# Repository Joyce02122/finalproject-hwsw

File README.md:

# DreamGuard: PTSD Lucid Dreaming Aid

The DreamGuard is a wearable device that helps people with PTSD manage nightmares using lucid dreaming techniques. It detects nightmares through heart rate or MPU6050 sensors and uses gentle light or sound stimuli to trigger awareness, allowing users to regain control. This device aims to reduce emotional distress, improving sleep quality and emotional resilience in PTSD sufferers.

## Sensor Device

## Display Device

## Device Communication and Diagram

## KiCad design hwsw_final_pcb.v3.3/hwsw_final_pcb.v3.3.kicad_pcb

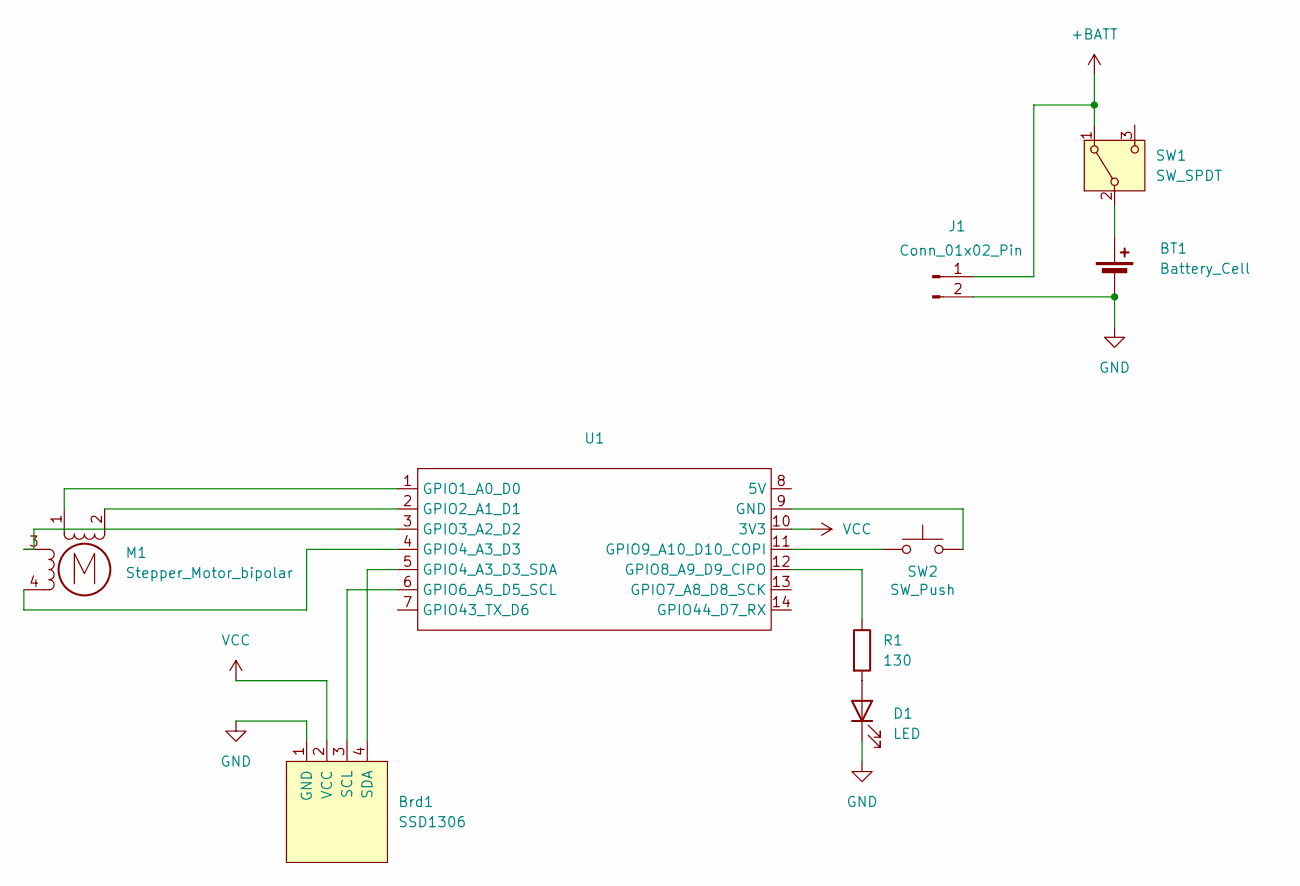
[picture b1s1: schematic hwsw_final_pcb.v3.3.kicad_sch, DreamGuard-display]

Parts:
BT1: Battery_Cell; JST_PH_B2B-PH-K_1x02_P2.00mm_Vertical
Brd1: SSD1306; 128x64OLED
D1: LED; LED_D5.0mm
J1: Conn_01x02_Pin; JST_PH_B2B-PH-K_1x02_P2.00mm_Vertical
M1: Stepper_Motor_bipolar; x27_stepper
R1: 130; R_0805_2012Metric
SW1: SW_SPDT; PinHeader_1x03_P2.54mm_Vertical
SW2: SW_Push; SW_PUSH-12mm
U1: XIAO_ESP32_SENSE

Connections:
+BATT: J1.1, SW1.1 (A)
GND: BT1.2 (-), Brd1.1 (GND), D1.1 (K), J1.2
unnamed: BT1.1 (+), SW1.2 (B)
unnamed: Brd1.3 (SCL), U1.6 (GPIO6_A5_D5_SCL)
unnamed: Brd1.4 (SDA), U1.5 (GPIO4_A3_D3_SDA)
unnamed: D1.2 (A), R1.2
unnamed: M1.2 (-), U1.2 (GPIO2_A1_D1)
unnamed: SW2.2, U1.9 (GND)
unnamed: M1.1, U1.1 (GPIO1_A0_D0)
unnamed: M1.3, U1.3 (GPIO3_A2_D2)
unnamed: M1.4, U1.4 (GPIO4_A3_D3)
unnamed: R1.1, U1.12 (GPIO8_A9_D9_CIPO)
unnamed: SW2.1, U1.11 (GPIO9_A10_D10_COPI)
VCC: Brd1.2 (VCC), U1.10 (3V3)

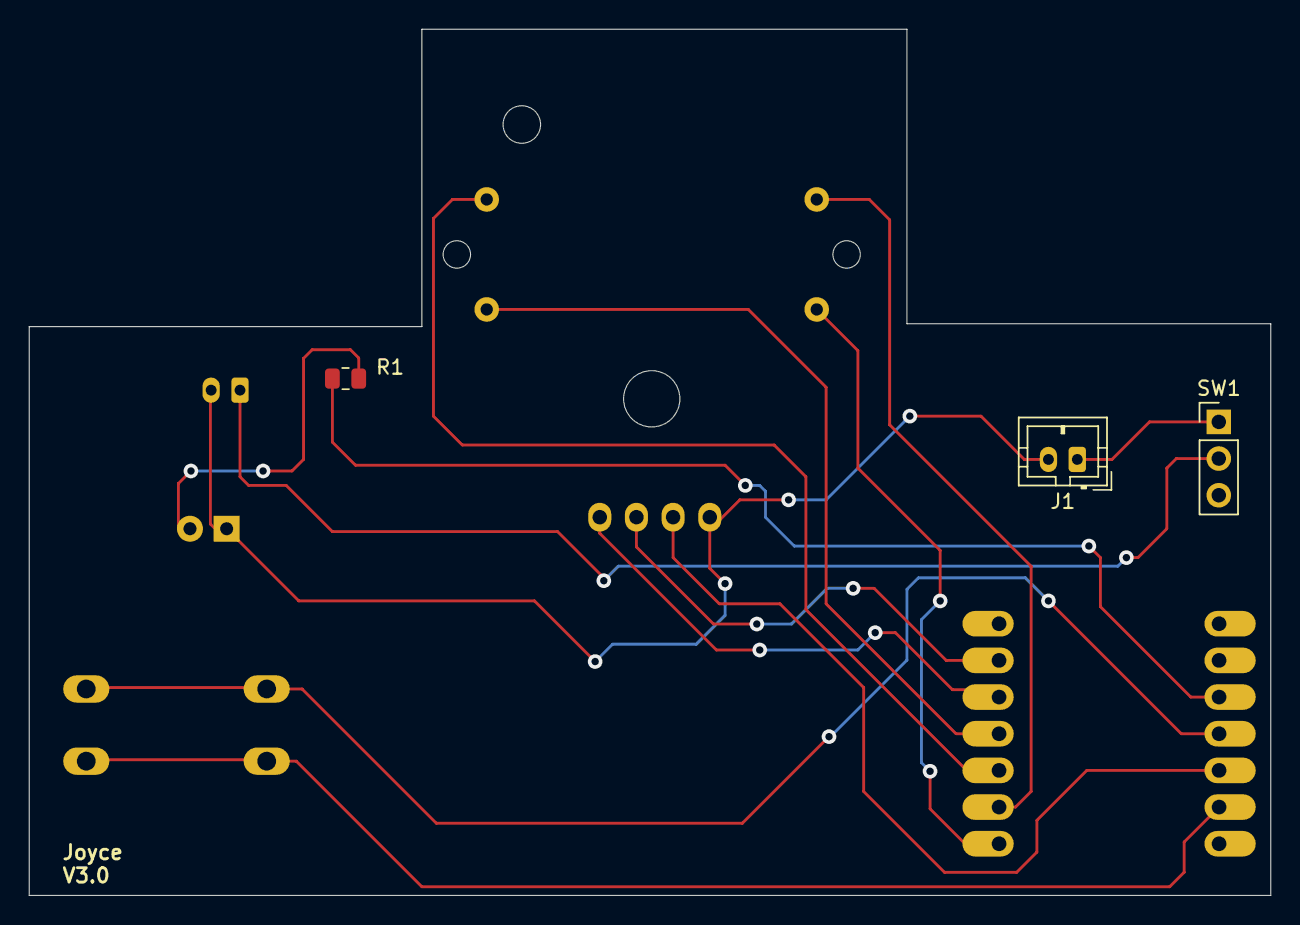
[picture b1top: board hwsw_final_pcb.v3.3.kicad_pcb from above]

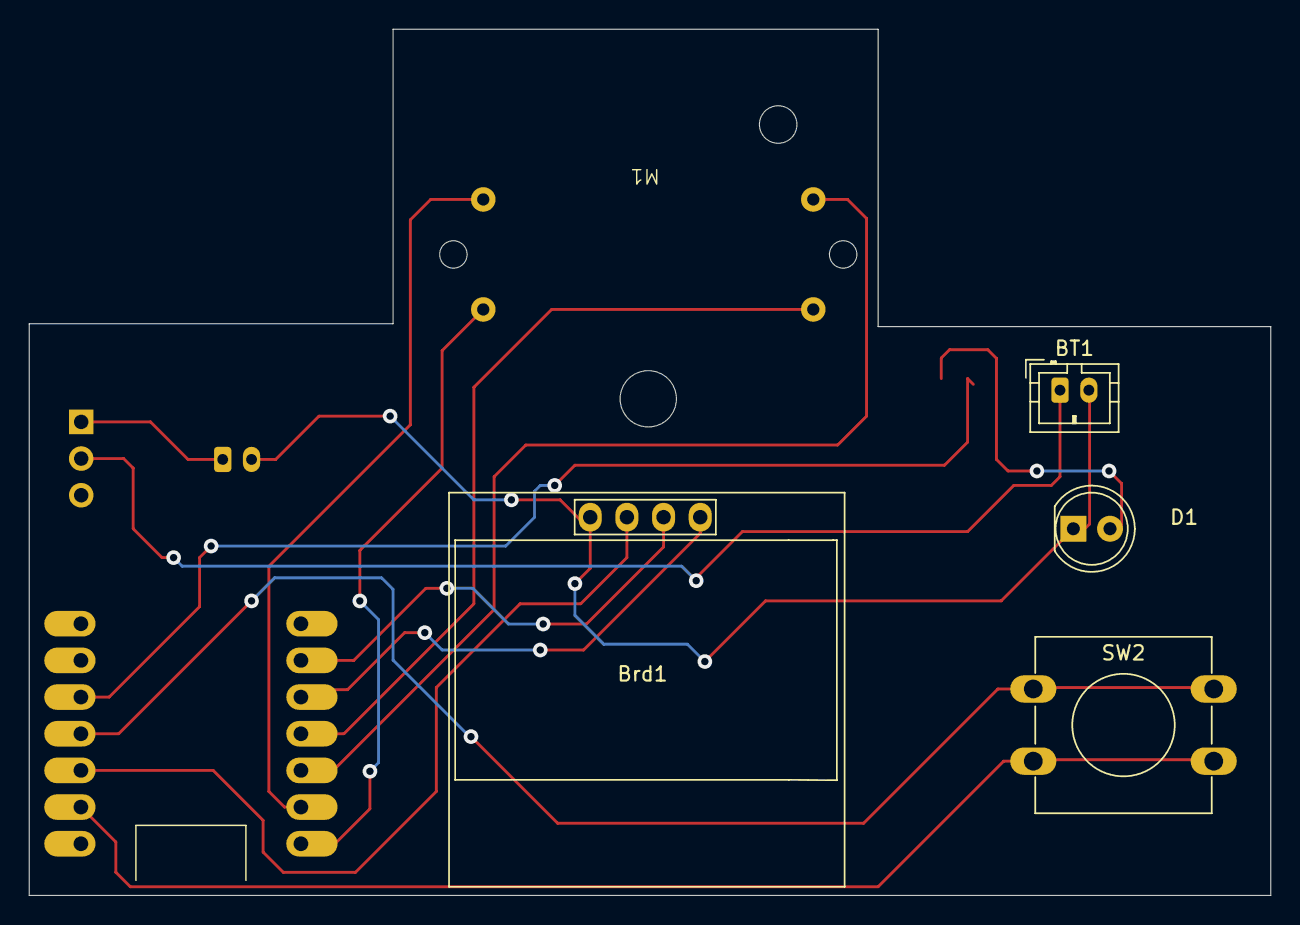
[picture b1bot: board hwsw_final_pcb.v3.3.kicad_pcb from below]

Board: 2 copper layers, 86.0 x 60.0 mm, 9 parts (6 on the bottom side), 14 nets.

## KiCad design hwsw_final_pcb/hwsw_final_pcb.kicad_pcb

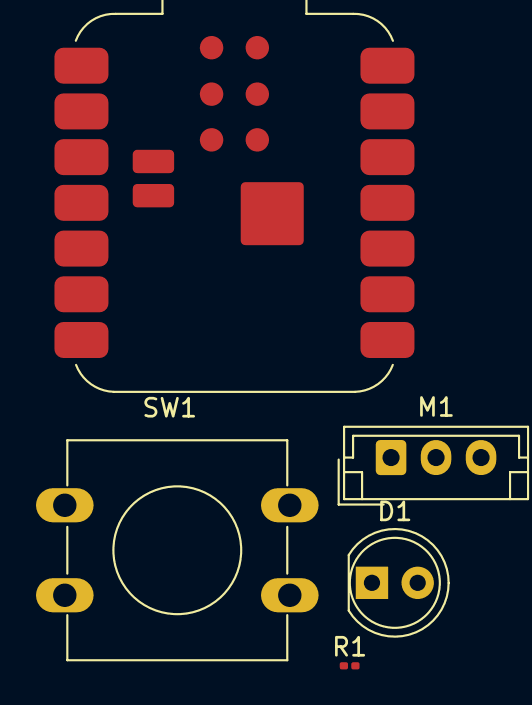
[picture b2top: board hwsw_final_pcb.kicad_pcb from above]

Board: 2 copper layers, 5 parts (0 on the bottom side), 6 nets, no tracks yet.

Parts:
D1: LED; LED_D5.0mm
M1: Stepper_Motor_bipolar; JST_EH_B3B-EH-A_1x03_P2.50mm_Vertical
R1: 200; R_0201_0603Metric
SW1: SW_SPDT; SW_PUSH-12mm
U4: SeeeduinoXIAO; MCU_Seeed_ESP32C3

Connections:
GND: D1.1 (K), U4.13 (GND)
unnamed: D1.2 (A), R1.2
unnamed: M1.2 (-), U4.2 (PA4_A1_D1)
unnamed: M1.1, U4.1 (PA02_A0_D0)
unnamed: M1.3, U4.3 (PA10_A2_D2)
VCC: SW1.2 (B), U4.14 (5V)

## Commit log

2025-01-22 first
2025-01-22 new readme
2025-01-29 Added KiCAD project hwsw_final_pcb
2025-02-14 datasheet
2025-02-14 Battery Life Estimate Spreadsheet
2025-03-12 new system architecture
2025-03-12 final pcb
